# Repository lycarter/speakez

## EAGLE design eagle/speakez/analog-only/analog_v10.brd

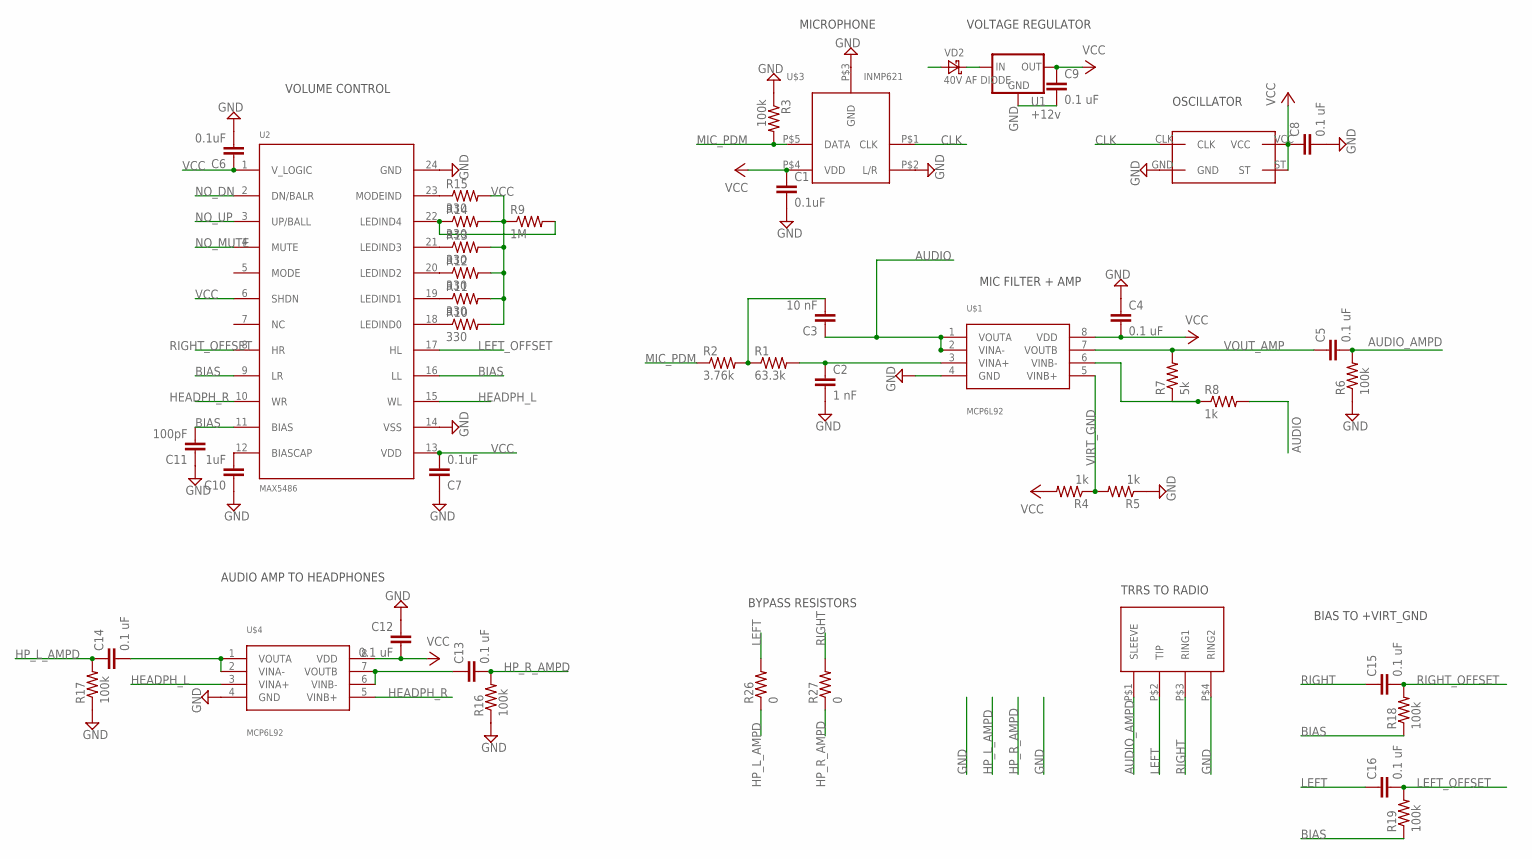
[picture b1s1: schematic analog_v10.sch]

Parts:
C1, C6, C7: 0.1uF; 0805
C2: 1 nF; 0805
C3: 10 nF; 0805
C4, C5, C8, C9, C12, C13, C14, C15, C16: 0.1 uF; 0805
C10: 1uF; 0805
C11: 100pF; 0805
R1: 63.3k; 0805
R2: 3.76k; 0805
R3, R6, R16, R17, R18, R19: 100k; 0805
R4, R5, R8: 1k; 0805
R7: 5k; 0805
R9: 1M; 0805
R10, R11, R12, R13, R14, R15: 330; 0805
R26, R27: 0; 0805
RADIO: SJ-43514-SMT; 35MM_SMD_4WIRE
U1: +12v; TO-252
U2: MAX5486; TSSOP24
U$1, U$4: MCP6L92; MSOP8
U$2: SG-210STF
U$3: INMP621; CUSTOM_MIC
VD2: 40V AF DIODE; SOD123

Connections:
AUDIO: C3.1, R8.2, U$1.1 (VOUTA), U$1.2 (VINA-)
AUDIO_AMPD: C5.2, R6.2, RADIO.P$1 (SLEEVE)
BIAS: C11.2, R18.1, R19.1, U2.9 (LR), U2.11 (BIAS), U2.16 (LL)
CLK: U$2.CLK, U$3.P$1 (CLK)
GND: C1.2, C2.2, C4.1, C6.2, C7.1, C8.2, C9.2, C10.1, C11.1, C12.1, R3.1, R5.1, R6.1, R16.1, R17.1, RADIO.P$4 (RING2), U1.3 (GND), U2.14 (VSS), U2.24 (GND), U$1.4 (GND), U$2.GND, U$3.P$2 (L/R), U$3.P$3 (GND), U$4.4 (GND)
HEADPH_L: U2.15 (WL), U$4.3 (VINA+)
HEADPH_R: U2.10 (WR), U$4.5 (VINB+)
HP_L_AMPD: C14.1, R17.2, R26.1
HP_R_AMPD: C13.2, R16.2, R27.1
LEFT: C16.1, R26.2, RADIO.P$2 (TIP)
LEFT_OFFSET: C16.2, R19.2, U2.17 (HL)
MIC_PDM: R2.1, R3.2, U$3.P$5 (DATA)
unnamed: C2.1, R1.2, U$1.3 (VINA+)
unnamed: C3.2, R1.1, R2.2
unnamed: R10.1, U2.18 (LEDIND0)
unnamed: R11.1, U2.19 (LEDIND1)
unnamed: R7.1, R8.1, U$1.6 (VINB-)
unnamed: R12.1, U2.20 (LEDIND2)
unnamed: R13.1, U2.21 (LEDIND3)
unnamed: C13.1, U$4.6 (VINB-), U$4.7 (VOUTB)
unnamed: R15.1, U2.23 (MODEIND)
unnamed: C10.2, U2.12 (BIASCAP)
unnamed: R9.2, R14.1, U2.22 (LEDIND4)
unnamed: C14.2, U$4.1 (VOUTA), U$4.2 (VINA-)
NO_DN: U2.2 (DN/BALR)
NO_MUTE: U2.4 (MUTE)
NO_UP: U2.3 (UP/BALL)
RIGHT: C15.1, R27.2, RADIO.P$3 (RING1)
RIGHT_OFFSET: C15.2, R18.2, U2.8 (HR)
VBAT: VD2.A
VBATSAFE: U1.2 (IN), VD2.C
VCC: C1.1, C4.2, C6.1, C7.2, C8.1, C9.1, C12.2, R4.2, R9.1, R10.2, R11.2, R12.2, R13.2, R14.2, R15.2, U1.1 (OUT), U2.1 (V_LOGIC), U2.6 (SHDN), U2.13 (VDD), U$1.8 (VDD), U$2.ST, U$2.VCC, U$3.P$4 (VDD), U$4.8 (VDD)
VIRT_GND: R4.1, R5.2, U$1.5 (VINB+)
VOUT_AMP: C5.1, R7.2, U$1.7 (VOUTB)

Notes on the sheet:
TRRS TO RADIO
BYPASS RESISTORS
AUDIO AMP TO HEADPHONES
VOLUME CONTROL
MIC FILTER + AMP
OSCILLATOR
MICROPHONE
VOLTAGE REGULATOR
BIAS TO +VIRT_GND

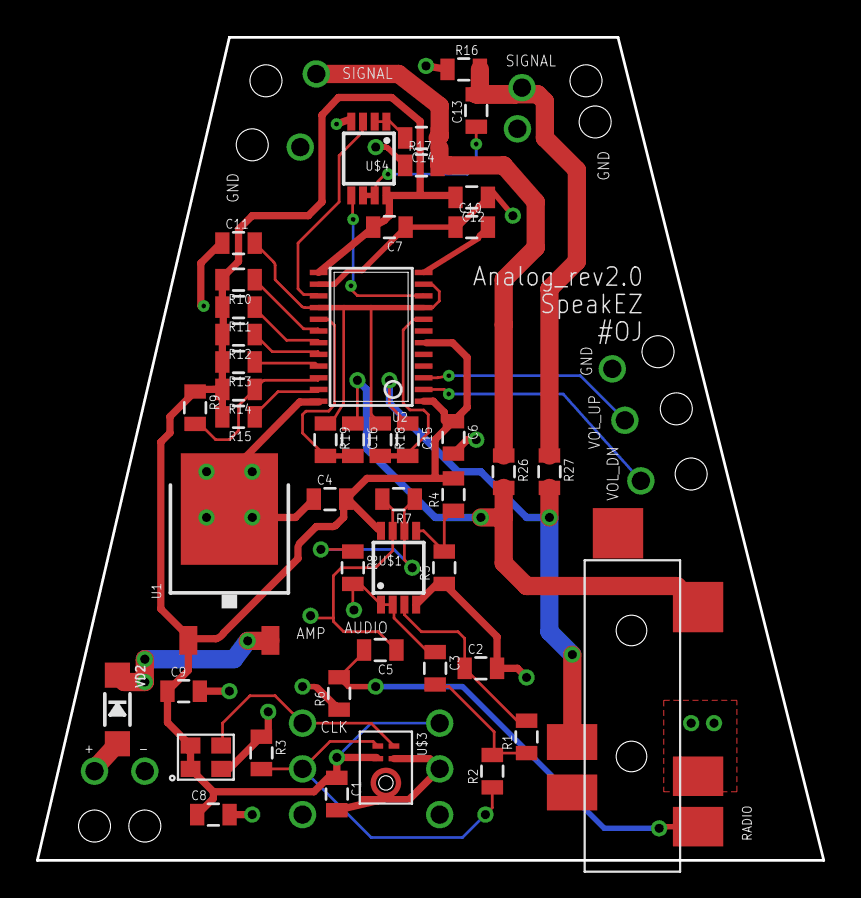
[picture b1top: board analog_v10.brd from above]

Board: 2 copper layers, 43.7 x 45.7 mm, 45 parts (0 on the bottom side), 30 nets.

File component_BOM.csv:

"Part";"Value";"Device";"Package";"Description";"PROD_ID";"VALUE";
"C1";"0.1uF";"CAP0805";"0805";"Capacitor";"";"";
"C2";"1 nF";"CAP0805";"0805";"Capacitor";"";"";
"C3";"10 nF";"CAP0805";"0805";"Capacitor";"";"";
"C4";"0.1 uF";"CAP0805";"0805";"Capacitor";"";"";
"C5";"0.1 uF";"CAP0805";"0805";"Capacitor";"";"";
"C6";"0.1uF";"CAP0805";"0805";"Capacitor";"";"";
"C7";"0.1uF";"CAP0805";"0805";"Capacitor";"";"";
"C8";"0.1 uF";"CAP0805";"0805";"Capacitor";"";"";
"C9";"0.1 uF";"CAP0805";"0805";"Capacitor";"";"";
"C10";"1uF";"CAP0805";"0805";"Capacitor";"";"";
"C11";"100pF";"CAP0805";"0805";"Capacitor";"";"";
"C12";"0.1 uF";"CAP0805";"0805";"Capacitor";"";"";
"C13";"0.1 uF";"CAP0805";"0805";"Capacitor";"";"";
"C14";"0.1 uF";"CAP0805";"0805";"Capacitor";"";"";
"C15";"0.1 uF";"CAP0805";"0805";"Capacitor";"";"";
"C16";"0.1 uF";"CAP0805";"0805";"Capacitor";"";"";
"R1";"63.3k";"RESISTOR0805-RES";"0805";"Resistor";"";"";
"R2";"3.76k";"RESISTOR0805-RES";"0805";"Resistor";"";"";
"R3";"100k";"RESISTOR0805-RES";"0805";"Resistor";"";"";
"R4";"1k";"RESISTOR0805-RES";"0805";"Resistor";"";"";
"R5";"1k";"RESISTOR0805-RES";"0805";"Resistor";"";"";
"R6";"100k";"RESISTOR0805-RES";"0805";"Resistor";"";"";
"R7";"5k";"RESISTOR0805-RES";"0805";"Resistor";"";"";
"R8";"1k";"RESISTOR0805-RES";"0805";"Resistor";"";"";
"R9";"1M";"RESISTOR0805-RES";"0805";"Resistor";"";"";
"R10";"330";"RESISTOR0805-RES";"0805";"Resistor";"";"";
"R11";"330";"RESISTOR0805-RES";"0805";"Resistor";"";"";
"R12";"330";"RESISTOR0805-RES";"0805";"Resistor";"";"";
"R13";"330";"RESISTOR0805-RES";"0805";"Resistor";"";"";
"R14";"330";"RESISTOR0805-RES";"0805";"Resistor";"";"";
"R15";"330";"RESISTOR0805-RES";"0805";"Resistor";"";"";
"R16";"100k";"RESISTOR0805-RES";"0805";"Resistor";"";"";
"R17";"100k";"RESISTOR0805-RES";"0805";"Resistor";"";"";
"R18";"100k";"RESISTOR0805-RES";"0805";"Resistor";"";"";
"R19";"100k";"RESISTOR0805-RES";"0805";"Resistor";"";"";
"R26";"0";"RESISTOR0805-RES";"0805";"Resistor";"";"";
"R27";"0";"RESISTOR0805-RES";"0805";"Resistor";"";"";
"RADIO";"SJ-43514-SMT";"SJ-43514-SMT";"35MM_SMD_4WIRE";"";"";"";
"U$1";"MCP6L92";"MCP6L92";"MSOP8";"MCP6L91T-E/MS";"";"";
"U$2";"SG-210STF";"SG-210STF";"SG-210STF";"";"";"";
"U$3";"INMP621";"INMP621";"CUSTOM_MIC";"";"";"";
"U$4";"MCP6L92";"MCP6L92";"MSOP8";"MCP6L91T-E/MS";"";"";
"U1";"+12v";"V_REG_78XX7812";"TO-252";"Voltage Regulator";"VREG-12370";"+12v";
"U2";"MAX5486";"MAX5486";"TSSOP24";"Maxim's MAX3387E 3V, ±15kV ESD-Protected, AutoShutdown Plus RS-232 Transceiver for PDAs and Cell Phones";"";"";
"VD2";"40V AF DIODE";"DIODE-SCHOTTKY-SOD123";"SOD123";"SCHOTTKY DIODE";"";"";

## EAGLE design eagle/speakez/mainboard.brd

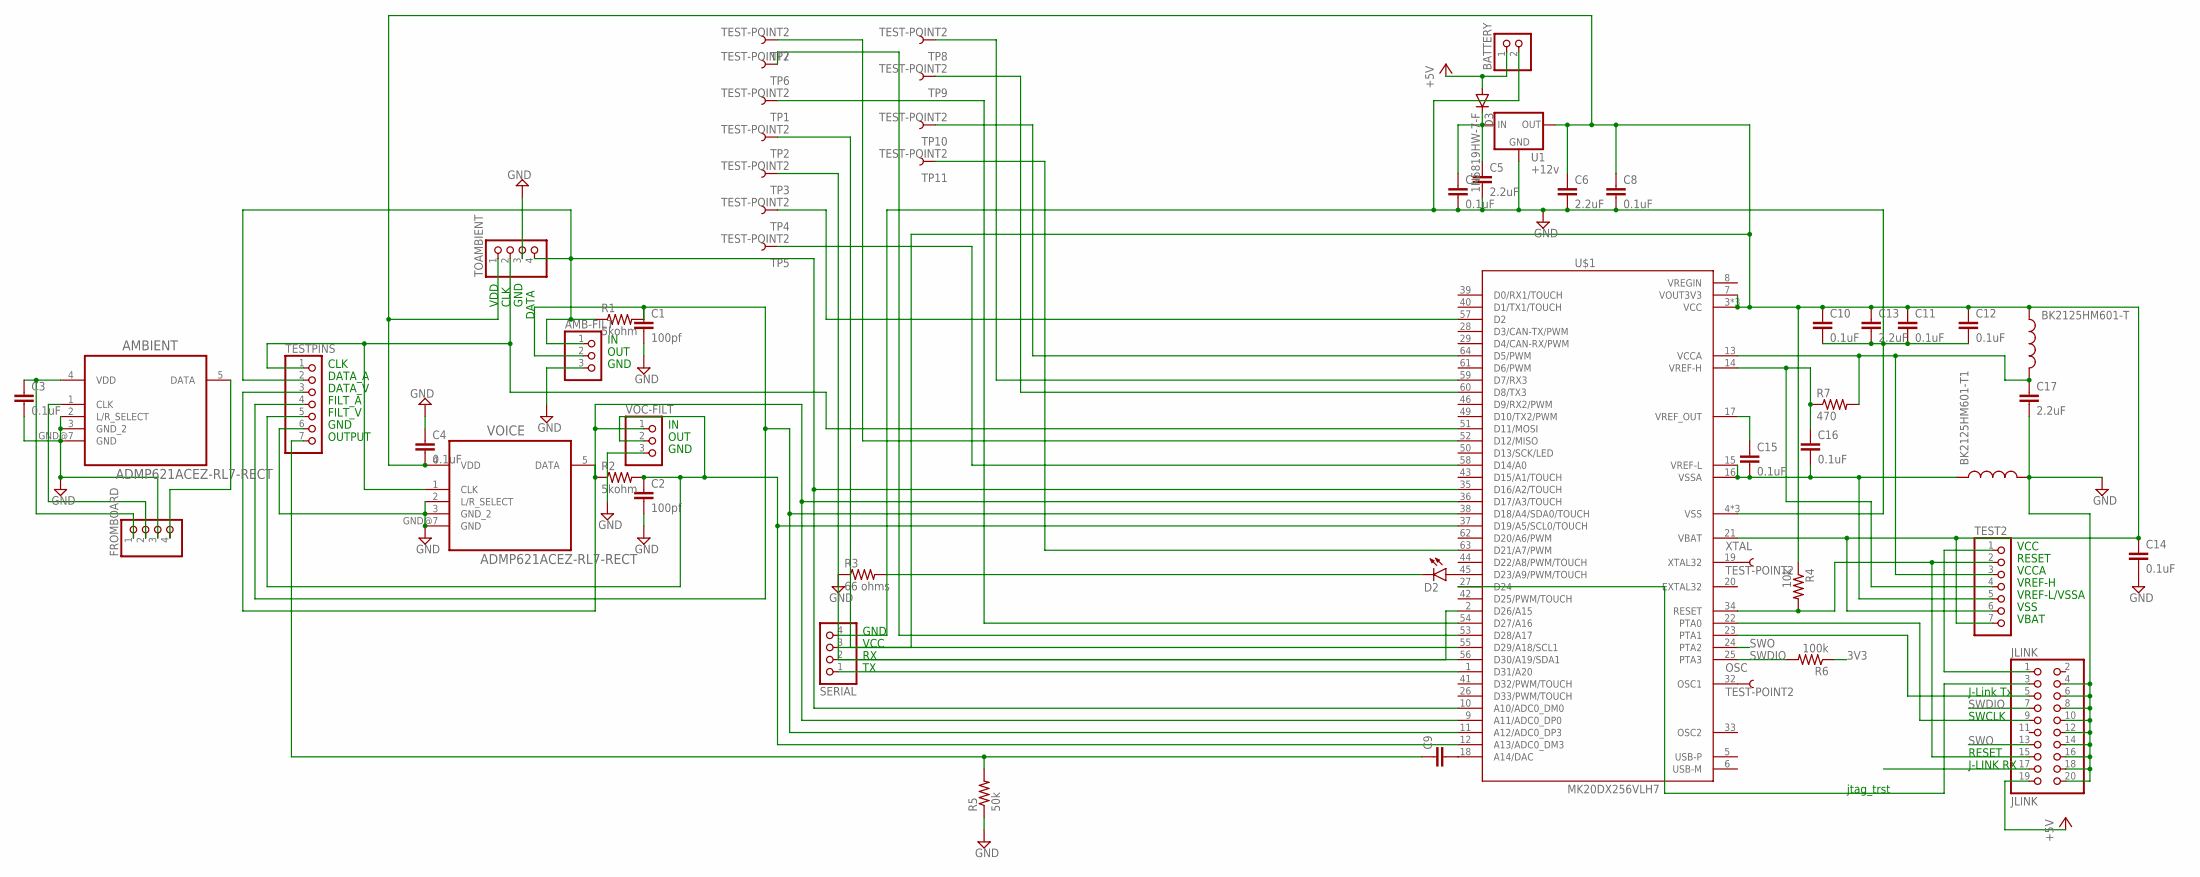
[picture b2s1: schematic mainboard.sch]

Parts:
AMB-FILT: PINHD-1X3; 1X03
AMBIENT: ADMP621ACEZ-RL7-RECT
BATTERY: PINHD-1X2; 1X02
BK2125HM601-T, BK2125HM601-T1: INDUCTOR0805; 0805
C1, C2: 100pf; 0805
C3, C4, C7, C8, C10, C11, C12, C14, C15, C16: 0.1uF; 0805
C5, C6, C13, C17: 2.2uF; 0805
C9: CAP0805; 0805
D2: LED1206; LED-1206
D3: 1N5819HW-7-F; SOD-123
FROMBOARD: PINHD-1X4; 1X04
JLINK: JLINK; 2X10
OSC: TEST-POINT2; PAD.02X.02
R1, R2: 5kohm; 0805
R3: 66 ohms; 0805
R4: 10k; 0805
R5: 50k; 0805
R6: 100k; 0805
R7: 470; 0805
SERIAL: PINHD-1X4; 1X04
TEST2: PINHD-1X7; 1X07
TESTPINS: PINHD-1X7; 1X07
TOAMBIENT: PINHD-1X4M; 1X04M
TP1, TP2, TP3, TP4, TP5, TP6, TP7, TP8, TP9, TP10, TP11: TEST-POINT2; PAD.02X.02
U1: +12v; TO-252
U$1: MK20DX256VLH7; QFP50P1200X1200X160-64N
VOC-FILT: PINHD-1X3; 1X03
VOICE: ADMP621ACEZ-RL7-RECT
XTAL: TEST-POINT2; PAD.02X.02

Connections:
3V3: R6.1
+5V: BATTERY.1, D3.A, JLINK.19
CLK: TESTPINS.1, TOAMBIENT.2, U$1.51 (D11/MOSI), VOICE.1 (CLK)
CLK2-A: AMBIENT.1 (CLK), FROMBOARD.2
DATA: R2.1, TESTPINS.3, U$1.9 (A11/ADC0_DP0), U$1.36 (D17/A3/TOUCH), VOC-FILT.1, VOICE.5 (DATA)
DATA2: AMB-FILT.1, R1.1, TESTPINS.2, TOAMBIENT.4, U$1.10 (A10/ADC0_DM0), U$1.35 (D16/A2/TOUCH)
DATA2-A: AMBIENT.5 (DATA), FROMBOARD.4
GND: AMB-FILT.3, AMBIENT.2 (L/R_SELECT), AMBIENT.3 (GND_2), AMBIENT.GND@7 (GND), BATTERY.2, BK2125HM601-T1.2, C1.2, C2.2, C3.2, C4.1, C5.2, C6.2, C7.2, C8.2, C10.2, C11.2, C12.2, C13.2, C14.2, C17.2, FROMBOARD.3, JLINK.4, JLINK.6, JLINK.8, JLINK.10, JLINK.12, JLINK.14, JLINK.16, JLINK.18, JLINK.20, R3.1, R5.1, SERIAL.4, TESTPINS.6, TOAMBIENT.3, U1.3 (GND), U$1.4 (VSS), U$1.31 (VSS), U$1.47 (VSS), VOC-FILT.3, VOICE.2 (L/R_SELECT), VOICE.3 (GND_2), VOICE.GND@7 (GND)
JTAG_TRST: JLINK.3, U$1.27 (D24)
unnamed: AMB-FILT.2, C1.1, R1.2, TESTPINS.4, U$1.11 (A12/ADC0_DP3), U$1.38 (D18/A4/SDA0/TOUCH)
unnamed: C2.1, R2.2, TESTPINS.5, U$1.12 (A13/ADC0_DM3), U$1.37 (D19/A5/SCL0/TOUCH), VOC-FILT.2
unnamed: TP7.P$1, U$1.52 (D12/MISO)
unnamed: TP6.P$1, U$1.53 (D28/A17)
unnamed: TP1.P$1, U$1.54 (D27/A16)
unnamed: TP2.P$1, U$1.55 (D29/A18/SCL1)
unnamed: TP3.P$1, U$1.56 (D30/A19/SDA1)
unnamed: TP4.P$1, U$1.57 (D2)
unnamed: TP5.P$1, U$1.58 (D14/A0)
unnamed: TP8.P$1, U$1.59 (D7/RX3)
unnamed: TP9.P$1, U$1.60 (D8/TX3)
unnamed: JLINK.5, U$1.23 (PTA1)
unnamed: JLINK.9, U$1.22 (PTA0)
unnamed: C5.1, C7.1, D3.C, U1.2 (IN)
unnamed: JLINK.1, TEST2.1
unnamed: D2.A, U$1.45 (D23/A9/PWM/TOUCH)
unnamed: TP10.P$1, U$1.64 (D5/PWM)
unnamed: D2.C, R3.2
unnamed: BK2125HM601-T1.1, C15.2, C16.2, TEST2.5, U$1.15 (VREF-L), U$1.16 (VSSA)
unnamed: TP11.P$1, U$1.63 (D21/A7/PWM)
unnamed: C16.1, R7.1, TEST2.4, U$1.14 (VREF-H)
unnamed: U$1.19 (XTAL32), XTAL.P$1
unnamed: SERIAL.1, U$1.1 (D31/A20)
unnamed: SERIAL.2, U$1.2 (D26/A15)
unnamed: C9.2, U$1.18 (A14/DAC)
unnamed: C9.1, R5.2, TESTPINS.7
unnamed: OSC.P$1, U$1.32 (OSC1)
unnamed: BK2125HM601-T.2, C17.1, R7.2, TEST2.3, U$1.13 (VCCA)
unnamed: C15.1, U$1.17 (VREF_OUT)
RESET: JLINK.15, R4.2, TEST2.2, U$1.34 (RESET)
SWDIO: JLINK.7, R6.2, U$1.25 (PTA3)
SWO: JLINK.13, U$1.24 (PTA2)
VDD-DECOUP: BK2125HM601-T.1, C4.2, C6.1, C8.1, C10.1, C11.1, C12.1, C13.1, C14.1, R4.1, SERIAL.3, TEST2.6, TEST2.7, TOAMBIENT.1, U1.1 (OUT), U$1.3 (VCC), U$1.7 (VOUT3V3), U$1.21 (VBAT), U$1.30 (VCC), U$1.48 (VCC), VOICE.4 (VDD)
VDD-DECOUP-A: AMBIENT.4 (VDD), C3.1, FROMBOARD.1

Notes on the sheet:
VDD
DATA
GND
CLK
VCC
DATA_A
DATA_V
FILT_A
FILT_V
OUTPUT
RESET
VCCA
VREF-H
VREF-L/VSSA
VBAT
VSS
J-Link Tx
SWCLK
J-LINK RX
jtag_trst
OUT

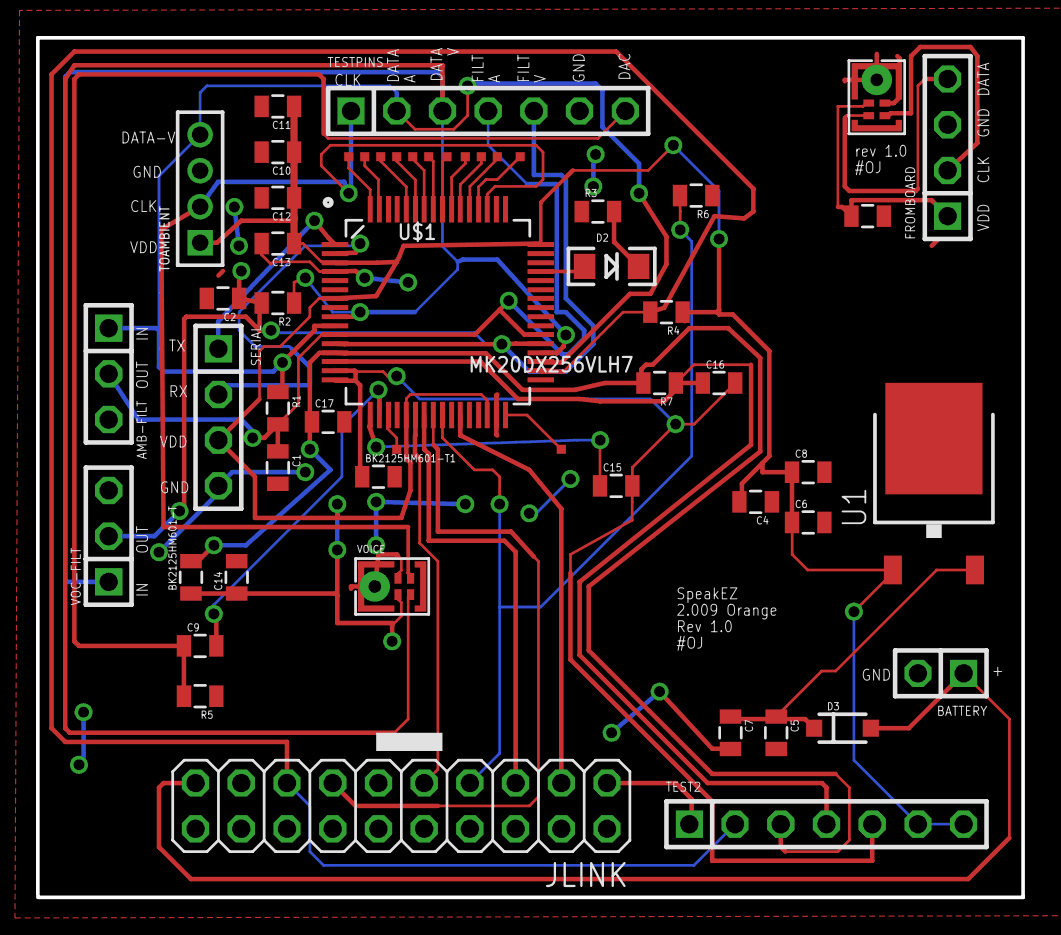
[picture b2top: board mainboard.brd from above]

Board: 2 copper layers, 54.7 x 47.8 mm, 54 parts (0 on the bottom side), 42 nets.

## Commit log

2016-11-04 initial commit
    files from assembly review
2016-11-05 add eagle project
    empty project/schematic
2016-11-05 add rc circuit to schematic
2016-11-05 correct capcitor value
    100pf for rc circuit, 0.1uf for decoupling cap
2016-11-05 added mics and breakout pins
    added both mics and test pins, also female pins for attaching teensy
    (remove if you were planning to just use a breadboard)
2016-11-05 Ribbon cable
    we were going to use a ribbon cable I think? I added headers for that
2016-11-06 change mic cap value, add battery header
    Changed mic cap to datasheet recommendation. Added screw terminals for
    battery + diode for protection
2016-11-06 Added board
    Added board, still needs to be routed
2016-11-06 Added GND to test pins
2016-11-06 Added decoupling cap
2016-11-06 Merge remote-tracking branch 'origin/master'
    # Conflicts:
    # eagle/speakez/mainboard.brd
    # eagle/speakez/mainboard.sch
2016-11-06 added decoupling cap to mic
    also kept clock pin as pin 11
2016-11-06 remap teensy pins
    move analog inputs to adc pins, switch 3.3v source, gnd source. add clk
    signal to digital output pin
2016-11-07 Added microcontroller
2016-11-07 Added battery stuff
    decoupling caps for battery with Fiona
2016-11-07 Added clock pin
    Still need to connect up headers but I can do that later
2016-11-07 changed clock
2016-11-07 disconnected battery from V3v3
2016-11-07 changed clock pin
2016-11-07 switched mic in to analog pins
2016-11-07 added 0.1uF caps
2016-11-07 re-added the differential pins
2016-11-07 connect VREFH and VBAT
2016-11-07 Added test LED
2016-11-07 added pull-up resistor to RESET
2016-11-07 added programmer for header
2016-11-07 added serial header connected to TX/RX
2016-11-07 added DAC cap + resistor
    didn't choose cap value yet. Sent output to a header test pin
2016-11-07 test pins for VCC and RESET
2016-11-07 Custom Teensy
    files from guy who made his own teensy
2016-11-07 add k20 reference pdf
2016-11-08 Added correct header for programmer
2016-11-08 added decoupling caps
    to microcontroller VCC pin
2016-11-08 finished copying over Teensy schematic
    Added a few more caps and ferrite beads to the microcontroller pins. I
    didn't connect VREF-H directly to VBAT. Added test pins.
2016-11-08 0.05" header to 0.1" header
2016-11-08 update jlink connector
    also add jtag support
2016-11-08 started moving things around
    oh god so many passives
2016-11-09 added ground rectangle thing
2016-11-09 added teensy code for analog and digital clocks
2016-11-10 fixed analog write resolution
2016-11-10 added ground plane
2016-11-10 add serial printouts for the data input pin
2016-11-10 routed some of board
2016-11-10 update to interrupt-based design
    next step is probably hardware interrupts off the 3mhz clock?
2016-11-10 finished routing board
    Didn't check for overlaps yet. Need to fix mic library.
2016-11-10 attach interrupt to data pin
2016-11-10 started working on removing overlaps/clearance issues
    still many more to go :grin:
2016-11-10 tweaked some clearances
2016-11-11 fixed lots of clearance issues, added headers for filter testing
2016-11-11 resolved all conflicts. planning to add silkscreen next
2016-11-11 corrected battery and voltage regulator
2016-11-11 board all routed + silkcreening!!! :grin:
2016-11-11 added board dimensions + output GERBER files
2016-11-11 fixed routing to satisfy PCB manufacturer :grimacing:
2016-11-11 update board
    add sparkfun libraries
2016-11-11 added libraries :book:
2016-11-15 sound subtraction (no DC offset yet!)
2016-11-16 start kds project
2016-11-16 new kds project
    omg blink blink blink
2016-11-23 start on analog-only, no-subtraction board
2016-11-23 tiny wiring tweak
2016-11-24 Analog Rev 1
    also added a ton of library parts
2016-11-26 updated gitignore for KDS files
2016-11-26 add in ADC component, enable system oscillator 0 with clk frequency 3MHz
2016-11-28 ADC Working
2016-11-28 repository cleanup: removed metadata files
2016-11-28 added arduino code for tech review
2016-11-29 Revert "repository cleanup: removed metadata files"
    This reverts commit a6c6b12cbdce985896f290a856c78e4f95e6ce74.
2016-11-30 cleanup second try
2016-11-30 update gitignore to ignore generated code
2016-11-30 remove generated code
2016-12-01 fixed oscillator
2016-12-01 Safety diode
2016-12-02 Added headers for mic
2016-12-02 Added new library for volume control
2016-12-02 added volume control
2016-12-02 got rid of LED, now resistors
2016-12-02 added zero ohm resistors...just couldn't resist
2016-12-02 resized board
2016-12-02 all components on, ugly ugly routing
2016-12-02 update L/R buffering, offsets, naming conventions, move info from nets layer to info layer
2016-12-02 routed some of board
    but doubting my routing
2016-12-02 did some more layout, fixed some random things
2016-12-02 made some more progress, shrunk the board
    going to eat breakfast. yay first allnighter of 2.009
2016-12-02 arranged the offsetters
2016-12-02 tweaking things, clearing out some clearance errors
2016-12-02 fixed all clearance issues, unsure about some dimensions issues
2016-12-02 got rid of mute + headphone jack; added solder holes + strain relief
2016-12-02 routing tweaks
2016-12-02 fattened up traces
2016-12-03 few small tweaks, mostly silkscreen modifications. Added gerbers for pcb order
2016-12-03 final tweaks
2016-12-04 add BOM

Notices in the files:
parts and their libraries:
SparkFun-Passives: Licensing: Creative Commons ShareAlike 4.0 International - https://creativecommons.org/licenses/by-sa/4.0
